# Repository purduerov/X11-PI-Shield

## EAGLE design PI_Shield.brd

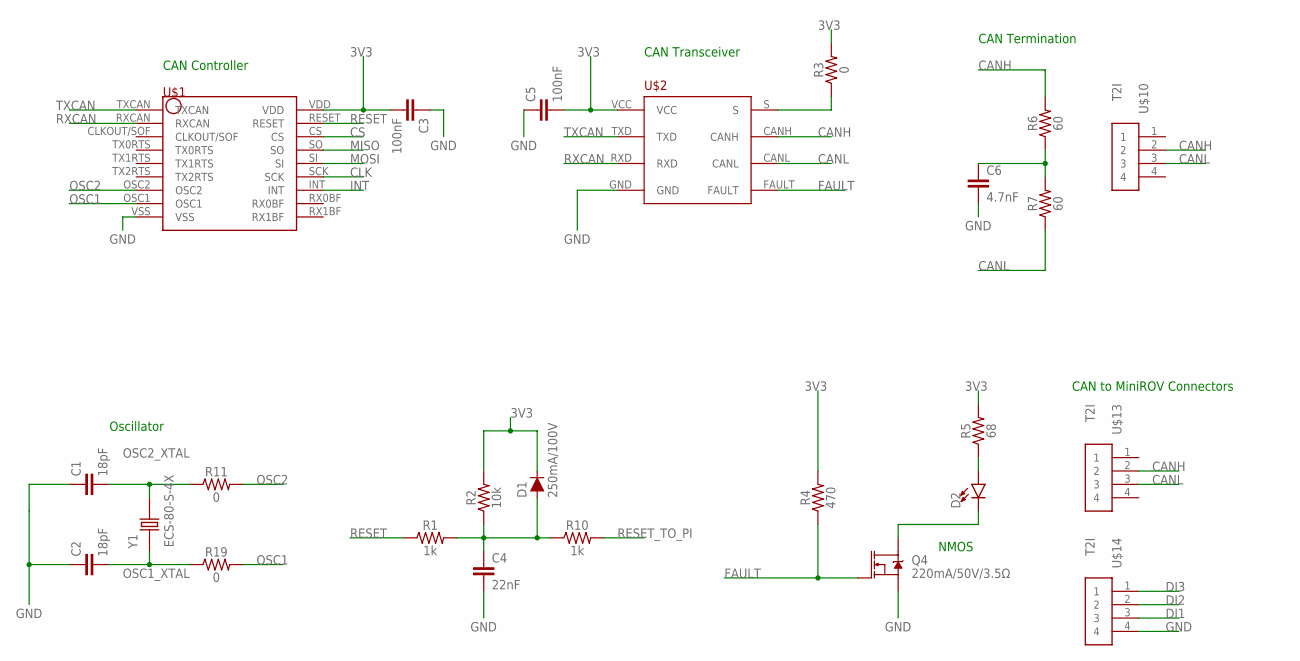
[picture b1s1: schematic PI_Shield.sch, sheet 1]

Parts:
C1, C2: 18pF; 0603
C3, C5: 100nF; 0603
C4: 22nF; 0603
C6: 4.7nF; 0603
D1: 250mA/100V; SOD-323
D2: LED0603; LED-0603
Q4: 220mA/50V/3.5Ω; SOT23-3
R1, R10: 1k; 0603
R2: 10k; 0603
R3, R11, R19: 0; 0603
R4: 470; 0603
R5: 68; 0603
R6, R7: 60; 0603
U$1: MCP2515
U$2: TCAN337D
U$10, U$13, U$14: T2I
Y1: ECS-80-S-4X; XTAL_ECS-80-S-4X

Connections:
3V3: C3.2, C5.2, D1.C, R2.2, R3.2, R4.2, R5.2, U$1.VDD, U$2.VCC; also elsewhere on the board
CANH: R6.2, U$2.CANH, U$10.2, U$13.2; also elsewhere on the board
CANL: R7.1, U$2.CANL, U$10.3, U$13.3; also elsewhere on the board
CLK: U$1.SCK; also elsewhere on the board
CS: U$1.CS; also elsewhere on the board
DI1: U$14.3; also elsewhere on the board
DI2: U$14.2; also elsewhere on the board
DI3: U$14.1; also elsewhere on the board
FAULT: Q4.1 (G), R4.1, U$2.FAULT
GND: C1.1, C2.1, C3.1, C4.2, C5.1, C6.2, Q4.2 (S), U$1.VSS, U$2.GND, U$14.4; also elsewhere on the board
INT: U$1.INT; also elsewhere on the board
MISO: U$1.SO; also elsewhere on the board
MOSI: U$1.SI; also elsewhere on the board
unnamed: R3.1, U$2.S
unnamed: C6.1, R6.1, R7.2
unnamed: C4.1, D1.A, R1.2, R2.1, R10.1
unnamed: D2.C, Q4.3 (D)
unnamed: D2.A, R5.1
OSC1: R19.2, U$1.OSC1
OSC1_XTAL: C2.2, R19.1, Y1.1
OSC2: R11.2, U$1.OSC2
OSC2_XTAL: C1.2, R11.1, Y1.2
RESET: R1.1, U$1.RESET
RESET_TO_PI: R10.2; also elsewhere on the board
RXCAN: U$1.RXCAN, U$2.RXD
TXCAN: U$1.TXCAN, U$2.TXD

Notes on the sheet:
NMOS
CAN Controller
CAN Transceiver
Oscillator
CAN Termination
CAN to MiniROV Connectors

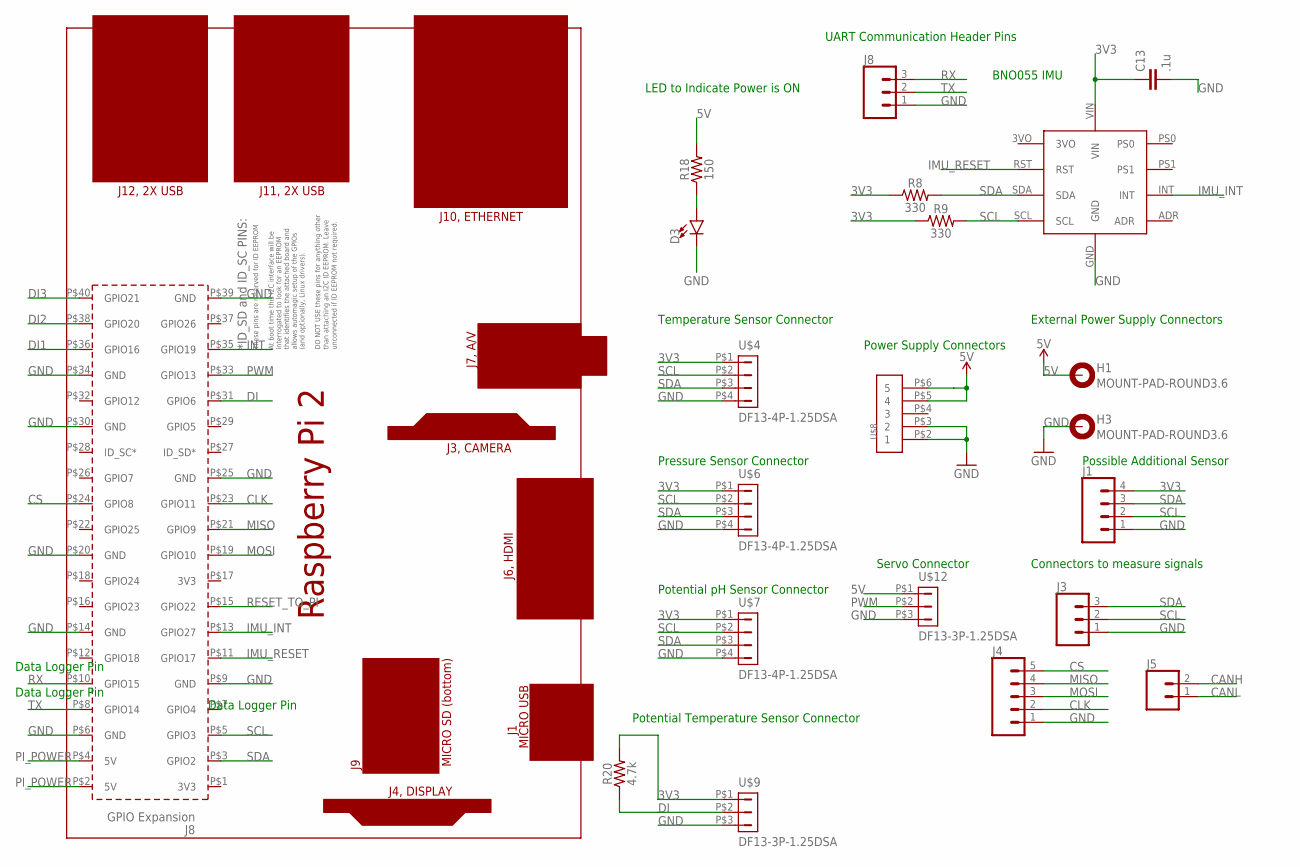
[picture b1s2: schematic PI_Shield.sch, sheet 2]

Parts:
C13: .1u; 0603
D3: LED0603; LED-0603
H1, H3: MOUNT-PAD-ROUND3.6; 3,6-PAD
J1: CONN_04; 1X04
J3, J8: CONN_03; 1X03
J4: CONN_05; 1X05
J5: CONN_02; 1X02
PCB1: RPI2
R8, R9: 330; 0603
R18: 150; 0603
R20: 4.7k; 0603
U$3: BNO055_9DOF_BREAKOUT; BNO055
U$4, U$6, U$7: DF13-4P-1.25DSA
U$8: T2I5P
U$9, U$12: DF13-3P-1.25DSA

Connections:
3V3: C13.1, J1.4, R8.1, R9.1, R20.2, U$3.VIN, U$4.P$1 (1), U$6.P$1 (1), U$7.P$1 (1), U$9.P$1 (1); also elsewhere on the board
5V: H1.B3,6, R18.2, U$8.P$5 (4), U$8.P$6 (5), U$12.P$1 (1); also elsewhere on the board
CANH: J5.2; also elsewhere on the board
CANL: J5.1; also elsewhere on the board
CLK: J4.2, PCB1.P$23 (GPIO11); also elsewhere on the board
CS: J4.5, PCB1.P$24 (GPIO8); also elsewhere on the board
DI: PCB1.P$31 (GPIO6), R20.1, U$9.P$2 (2)
DI1: PCB1.P$36 (GPIO16); also elsewhere on the board
DI2: PCB1.P$38 (GPIO20); also elsewhere on the board
DI3: PCB1.P$40 (GPIO21); also elsewhere on the board
GND: C13.2, D3.C, H3.B3,6, J1.1, J3.1, J4.1, J8.1, PCB1.P$6 (GND), PCB1.P$9 (GND), PCB1.P$14 (GND), PCB1.P$20 (GND), PCB1.P$25 (GND), PCB1.P$30 (GND), PCB1.P$34 (GND), PCB1.P$39 (GND), U$3.GND, U$4.P$4 (4), U$6.P$4 (4), U$7.P$4 (4), U$8.P$2 (1), U$8.P$3 (2), U$9.P$3 (3), U$12.P$3 (3); also elsewhere on the board
IMU_INT: PCB1.P$13 (GPIO27), U$3.INT
IMU_RESET: PCB1.P$11 (GPIO17), U$3.RST
INT: PCB1.P$35 (GPIO19); also elsewhere on the board
MISO: J4.4, PCB1.P$21 (GPIO9); also elsewhere on the board
MOSI: J4.3, PCB1.P$19 (GPIO10); also elsewhere on the board
unnamed: D3.A, R18.1
PI_POWER: PCB1.P$2 (5V), PCB1.P$4 (5V); also elsewhere on the board
PWM: PCB1.P$33 (GPIO13), U$12.P$2 (2)
RESET_TO_PI: PCB1.P$15 (GPIO22); also elsewhere on the board
RX: J8.3, PCB1.P$10 (GPIO15)
SCL: J1.2, J3.2, PCB1.P$5 (GPIO3), R9.2, U$3.SCL, U$4.P$2 (2), U$6.P$2 (2), U$7.P$2 (2); also elsewhere on the board
SDA: J1.3, J3.3, PCB1.P$3 (GPIO2), R8.2, U$3.SDA, U$4.P$3 (3), U$6.P$3 (3), U$7.P$3 (3); also elsewhere on the board
TX: J8.2, PCB1.P$8 (GPIO14)

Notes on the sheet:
Connectors to measure signals
Temperature Sensor Connector
Pressure Sensor Connector
Potential pH Sensor Connector
BNO055 IMU
External Power Supply Connectors
LED to Indicate Power is ON
Potential Temperature Sensor Connector
Power Supply Connectors
Data Logger Pin
Possible Additional Sensor
UART Communication Header Pins
Servo Connector

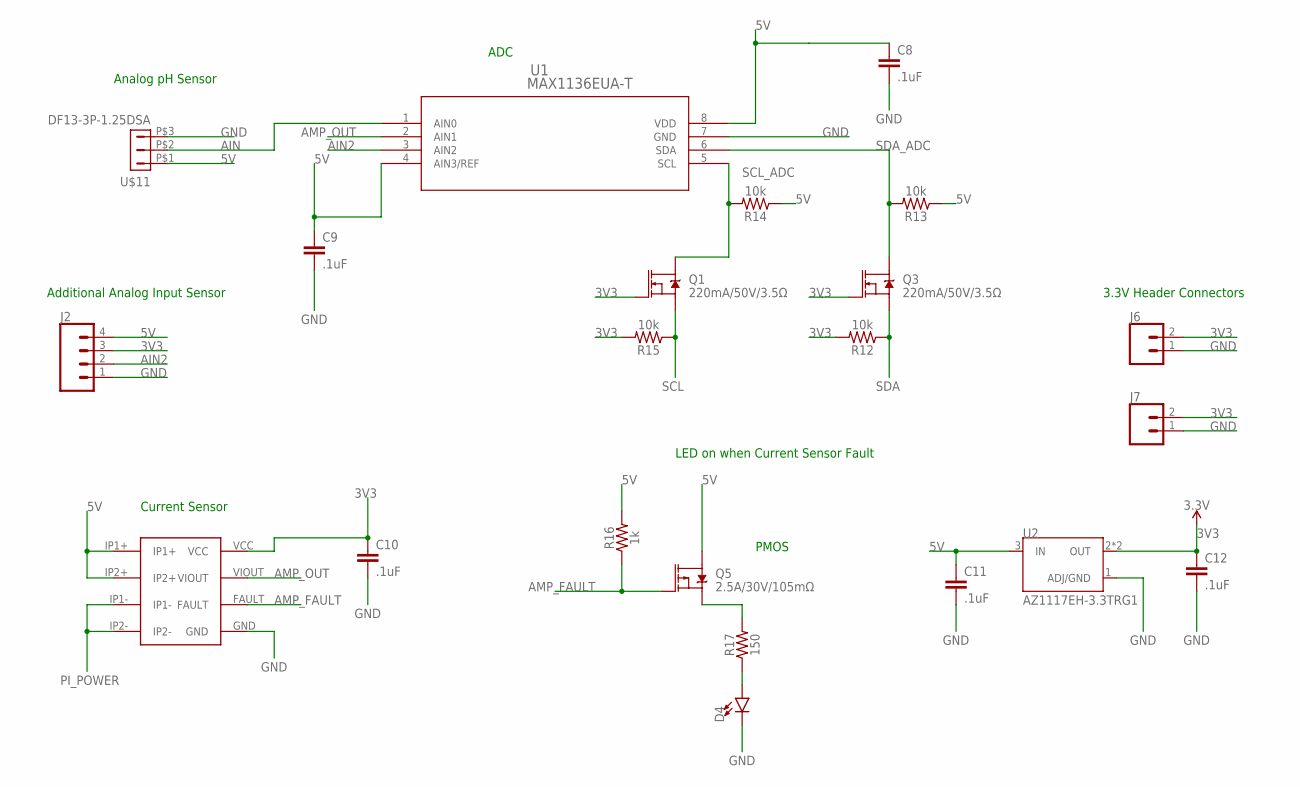
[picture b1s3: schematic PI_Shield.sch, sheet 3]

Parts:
C8, C9, C10, C11, C12: .1uF; 0603
D4: LED0603; LED-0603
J2: CONN_04; 1X04
J6, J7: CONN_02; 1X02
Q1, Q3: 220mA/50V/3.5Ω; SOT23-3
Q5: 2.5A/30V/105mΩ; SOT23-3
R12, R13, R14, R15: 10k; 0603
R16: 1k; 0603
R17: 150; 0603
U1: MAX1136EUA-T; 21-0036K
U2: AZ1117EH-3.3TRG1; SOT230P700X180-4N
U$5: ACS711
U$11: DF13-3P-1.25DSA

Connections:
3V3: C10.1, C12.1, J2.3, J6.2, J7.2, Q1.1 (G), Q3.1 (G), R12.2, R15.2, U2.2 (OUT), U2.4 (OUT), U$5.VCC; also elsewhere on the board
5V: C8.1, C9.1, C11.1, J2.4, Q5.3 (D), R13.1, R14.1, R16.2, U1.4 (AIN3/REF), U1.8 (VDD), U2.3 (IN), U$5.IP1+, U$5.IP2+, U$11.P$1 (1); also elsewhere on the board
AIN: U1.1 (AIN0), U$11.P$2 (2)
AIN2: J2.2, U1.3 (AIN2)
AMP_FAULT: Q5.1 (G), R16.1, U$5.FAULT
AMP_OUT: U1.2 (AIN1), U$5.VIOUT
GND: C8.2, C9.2, C10.2, C11.2, C12.2, D4.C, J2.1, J6.1, J7.1, U1.7 (GND), U2.1 (ADJ/GND), U$5.GND, U$11.P$3 (3); also elsewhere on the board
unnamed: Q5.2 (S), R17.2
unnamed: D4.A, R17.1
PI_POWER: U$5.IP1-, U$5.IP2-; also elsewhere on the board
SCL: Q1.2 (S), R15.1; also elsewhere on the board
SCL_ADC: Q1.3 (D), R14.2, U1.5 (SCL)
SDA: Q3.2 (S), R12.1; also elsewhere on the board
SDA_ADC: Q3.3 (D), R13.2, U1.6 (SDA)

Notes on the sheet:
Analog pH Sensor
PMOS
ADC
Current Sensor
LED on when Current Sensor Fault
Additional Analog Input Sensor
3.3V Header Connectors

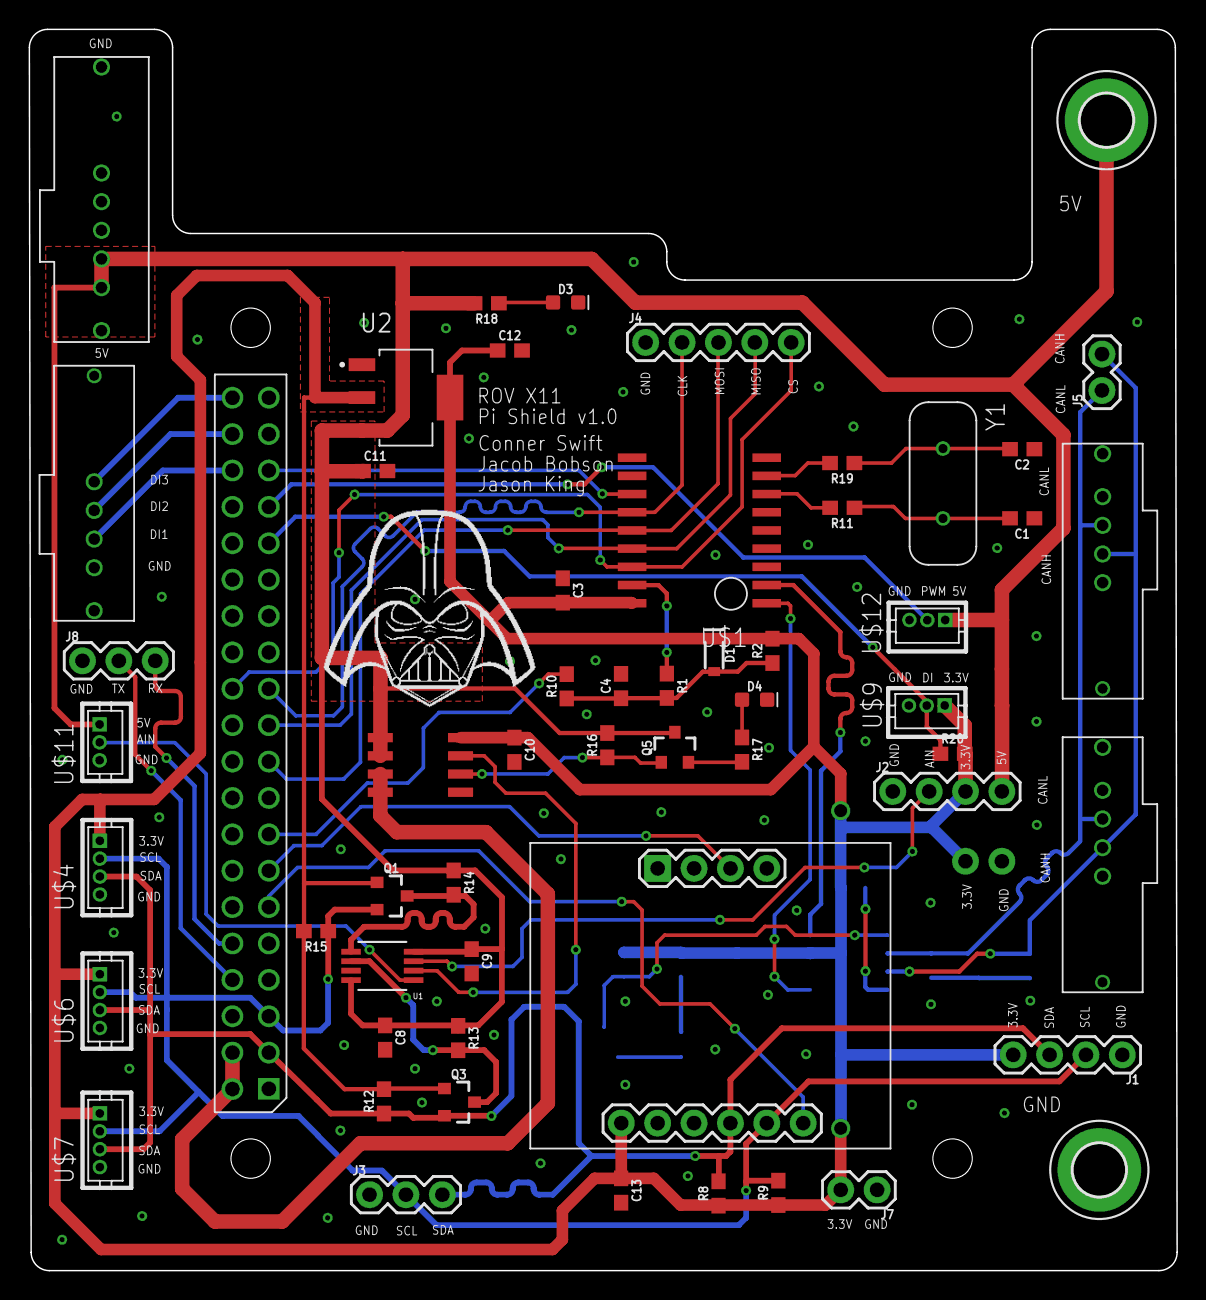
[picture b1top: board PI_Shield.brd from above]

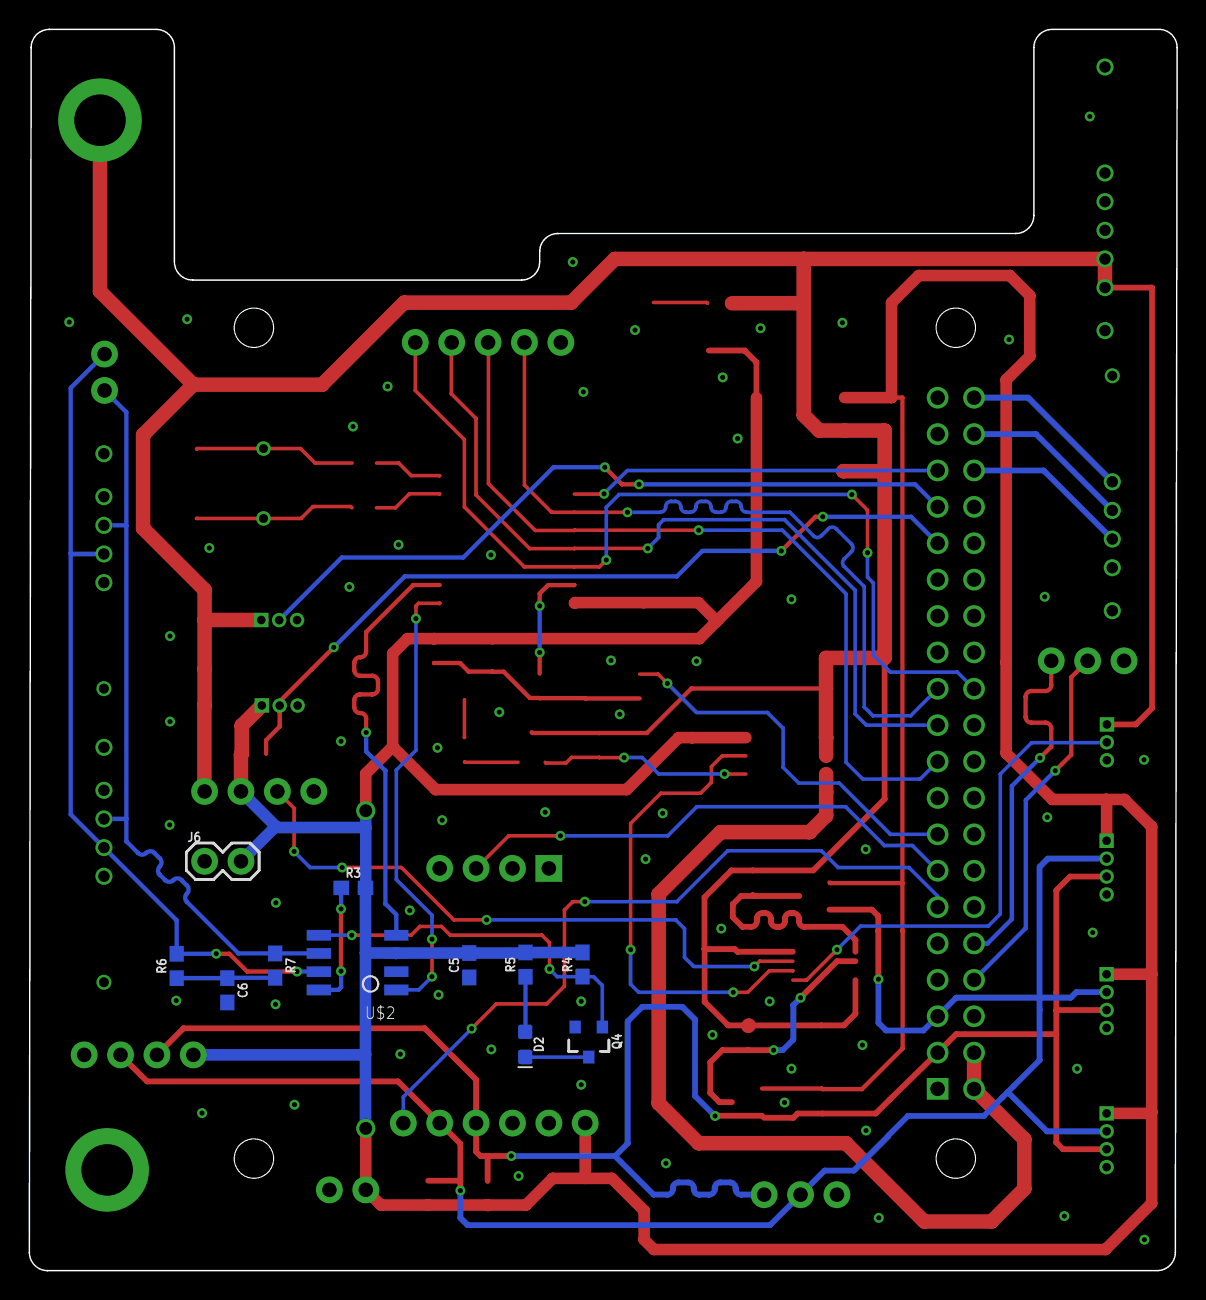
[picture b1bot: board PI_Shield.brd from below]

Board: 2 copper layers, 80.1 x 86.7 mm, 68 parts (11 on the bottom side), 45 nets.

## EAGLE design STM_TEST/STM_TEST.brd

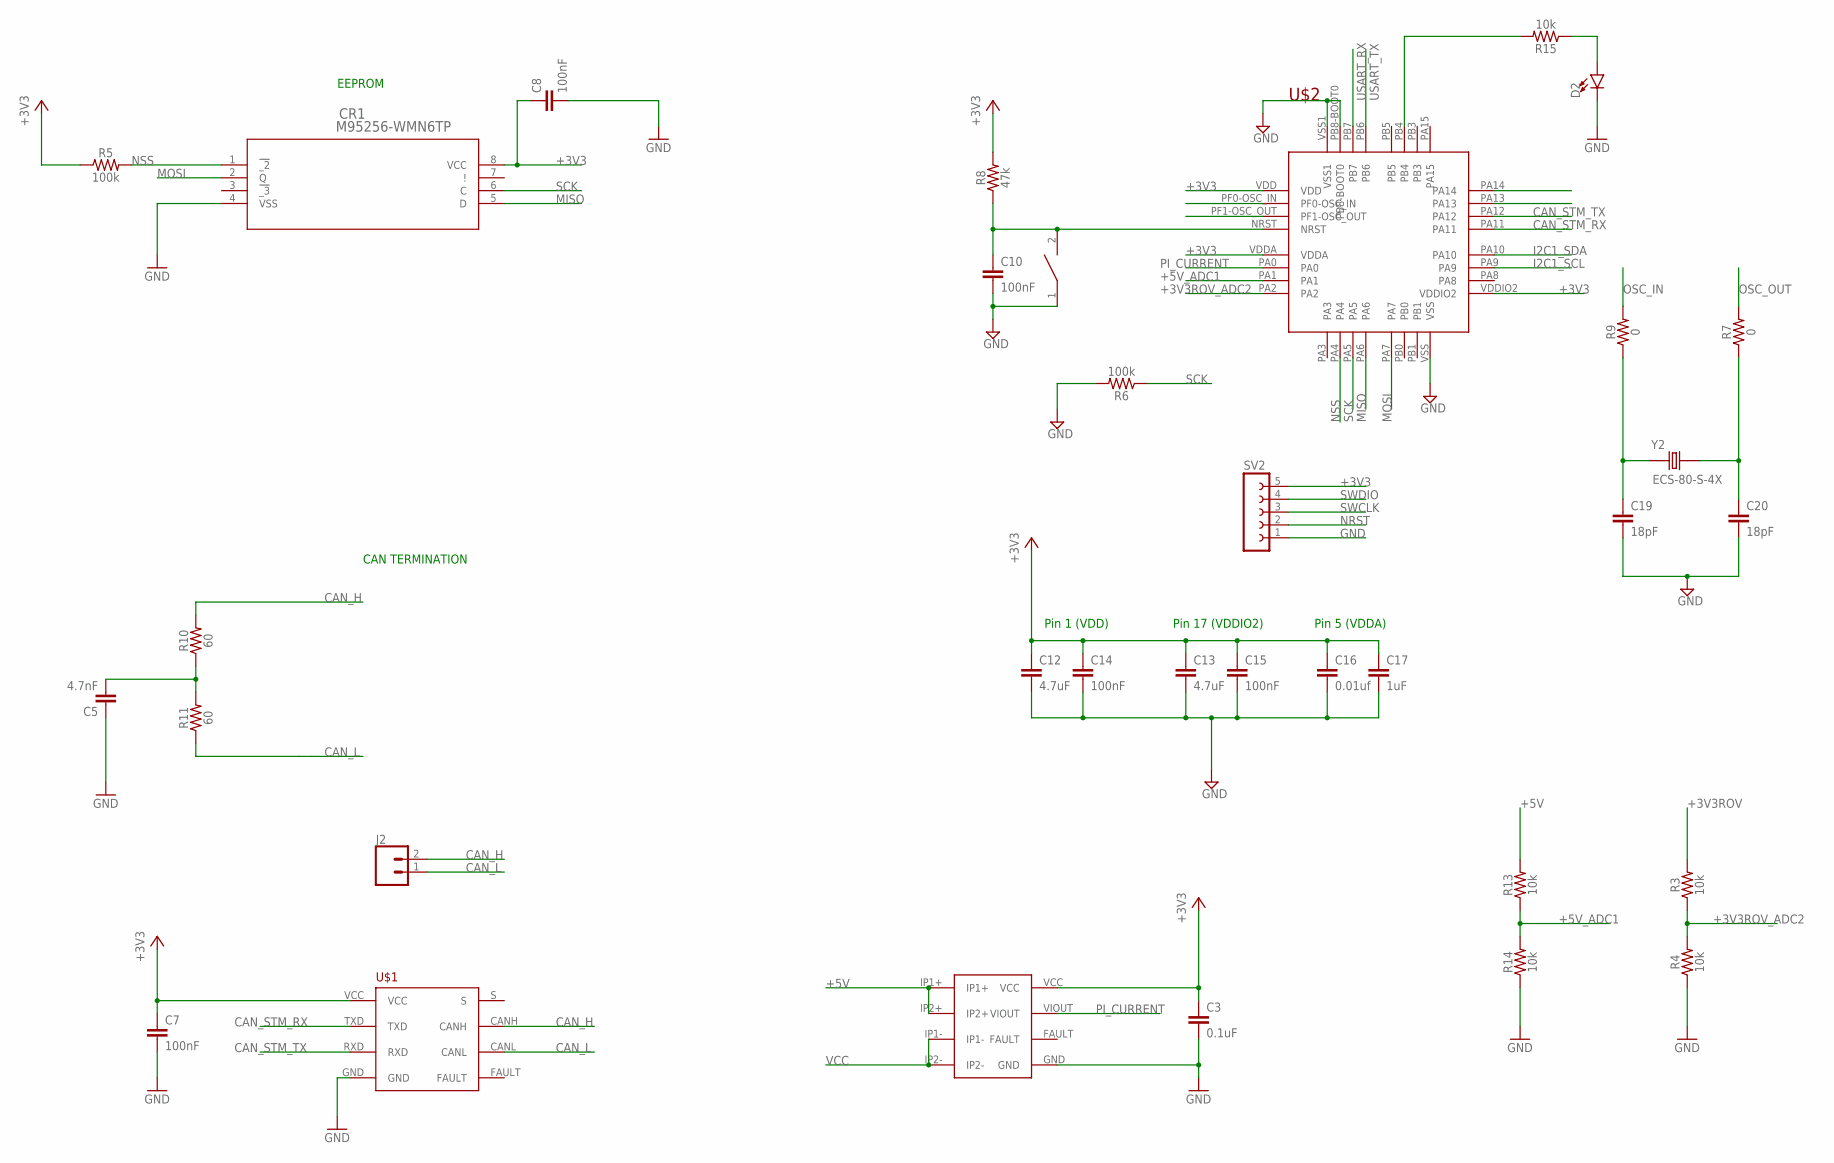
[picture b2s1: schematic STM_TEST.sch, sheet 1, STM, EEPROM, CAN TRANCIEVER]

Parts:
C3: 0.1uF; 0603
C5: 4.7nF; 0603
C7, C8, C10, C14, C15: 100nF; 0603
C12, C13: 4.7uF; 0603
C16: 0.01uf; 0603
C17: 1uF; 0603
C19, C20: 18pF; 0603
CR1: M95256-WMN6TP; SO-8
D2: LED0603; LED-0603
J2: CONN_02; 1X02
R3, R4, R13, R14, R15: 10k; 0603
R5, R6: 100k; 0603
R7, R9: 0; 0603
R8: 47k; 0603
R10, R11: 60; 0603
RESET1: SWITCH; SW_2512
SV2: FE05-1
U$1: TCAN337D
U$2: STM32F042K6T6
U$4: ACS711
Y2: ECS-80-S-4X; XTAL_ECS-80-S-4X

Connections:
+3V3: C3.1, C7.1, C8.1, C12.1, C13.1, C14.1, C15.1, C16.1, C17.1, CR1.8 (VCC), R5.1, R8.2, SV2.5, U$1.VCC, U$2.VDD, U$2.VDDA, U$2.VDDIO2, U$4.VCC; also elsewhere on the board
+3V3ROV: R3.2; also elsewhere on the board
+3V3ROV_ADC2: R3.1, R4.2, U$2.PA2
+5V: R13.2, U$4.IP1+, U$4.IP2+; also elsewhere on the board
+5V_ADC1: R13.1, R14.2, U$2.PA1
CAN_H: J2.2, R10.2, U$1.CANH; also elsewhere on the board
CAN_L: J2.1, R11.1, U$1.CANL; also elsewhere on the board
CAN_STM_RX: U$1.TXD, U$2.PA11
CAN_STM_TX: U$1.RXD, U$2.PA12
GND: C3.2, C5.1, C7.2, C8.2, C10.2, C12.2, C13.2, C14.2, C15.2, C16.2, C17.2, C19.2, C20.2, CR1.4 (VSS), D2.C, R4.1, R6.2, R14.1, RESET1.1, SV2.1, U$1.GND, U$2.PB8-BOOT0, U$2.VSS, U$2.VSS1, U$4.GND; also elsewhere on the board
I2C1_SCL: U$2.PA9; also elsewhere on the board
I2C1_SDA: U$2.PA10; also elsewhere on the board
MISO: CR1.5 (D), U$2.PA6
MOSI: CR1.2 (Q), U$2.PA7
unnamed: C5.2, R10.1, R11.2
unnamed: D2.A, R15.1
unnamed: R15.2, U$2.PB4
unnamed: C20.1, R7.1, Y2.2
unnamed: C19.1, R9.1, Y2.1
NRST: C10.1, R8.1, RESET1.2, SV2.2, U$2.NRST
NSS: CR1.1 (!_2), R5.2, U$2.PA4
OSC_IN: R9.2, U$2.PF0-OSC_IN
OSC_OUT: R7.2, U$2.PF1-OSC_OUT
PI_CURRENT: U$2.PA0, U$4.VIOUT
SCK: CR1.6 (C), R6.1, U$2.PA5
SWCLK: SV2.3, U$2.PA14
SWDIO: SV2.4, U$2.PA13
USART_RX: U$2.PB7; also elsewhere on the board
USART_TX: U$2.PB6; also elsewhere on the board
VCC: U$4.IP1-, U$4.IP2-; also elsewhere on the board

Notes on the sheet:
Pin 1 (VDD)
Pin 17 (VDDIO2)
Pin 5 (VDDA)
CAN TERMINATION
EEPROM

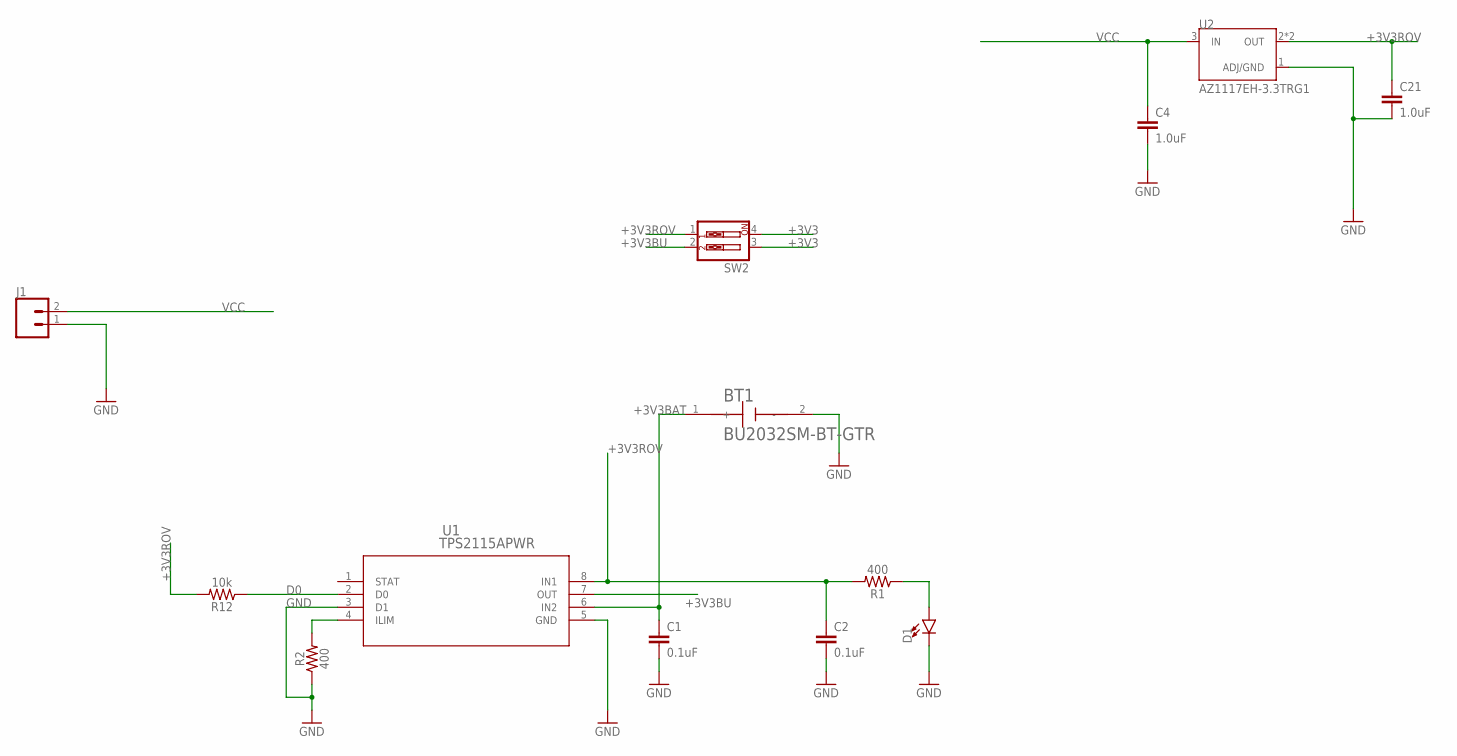
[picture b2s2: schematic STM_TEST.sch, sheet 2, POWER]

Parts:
BT1: BU2032SM-BT-GTR; BAT_BU2032SM-BT-GTR
C1, C2: 0.1uF; 0603
C4, C21: 1.0uF; 0603
D1: LED0603; LED-0603
J1: CONN_02; 1X02
R1, R2: 400; 0603
R12: 10k; 0603
SW2: SW_DIP-2; EDG-02
U1: TPS2115APWR; PW8
U2: AZ1117EH-3.3TRG1; SOT230P700X180-4N

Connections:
+3V3: SW2.3, SW2.4; also elsewhere on the board
+3V3BAT: BT1.1 (+), C1.1, U1.6 (IN2)
+3V3BU: SW2.2, U1.7 (OUT)
+3V3ROV: C2.1, C21.1, R1.2, R12.2, SW2.1, U1.8 (IN1), U2.2 (OUT), U2.4 (OUT); also elsewhere on the board
D0: R12.1, U1.2 (D0)
GND: BT1.2 (-), C1.2, C2.2, C4.2, C21.2, D1.C, J1.1, R2.1, U1.3 (D1), U1.5 (GND), U2.1 (ADJ/GND); also elsewhere on the board
unnamed: R2.2, U1.4 (ILIM)
unnamed: D1.A, R1.1
VCC: C4.1, J1.2, U2.3 (IN); also elsewhere on the board

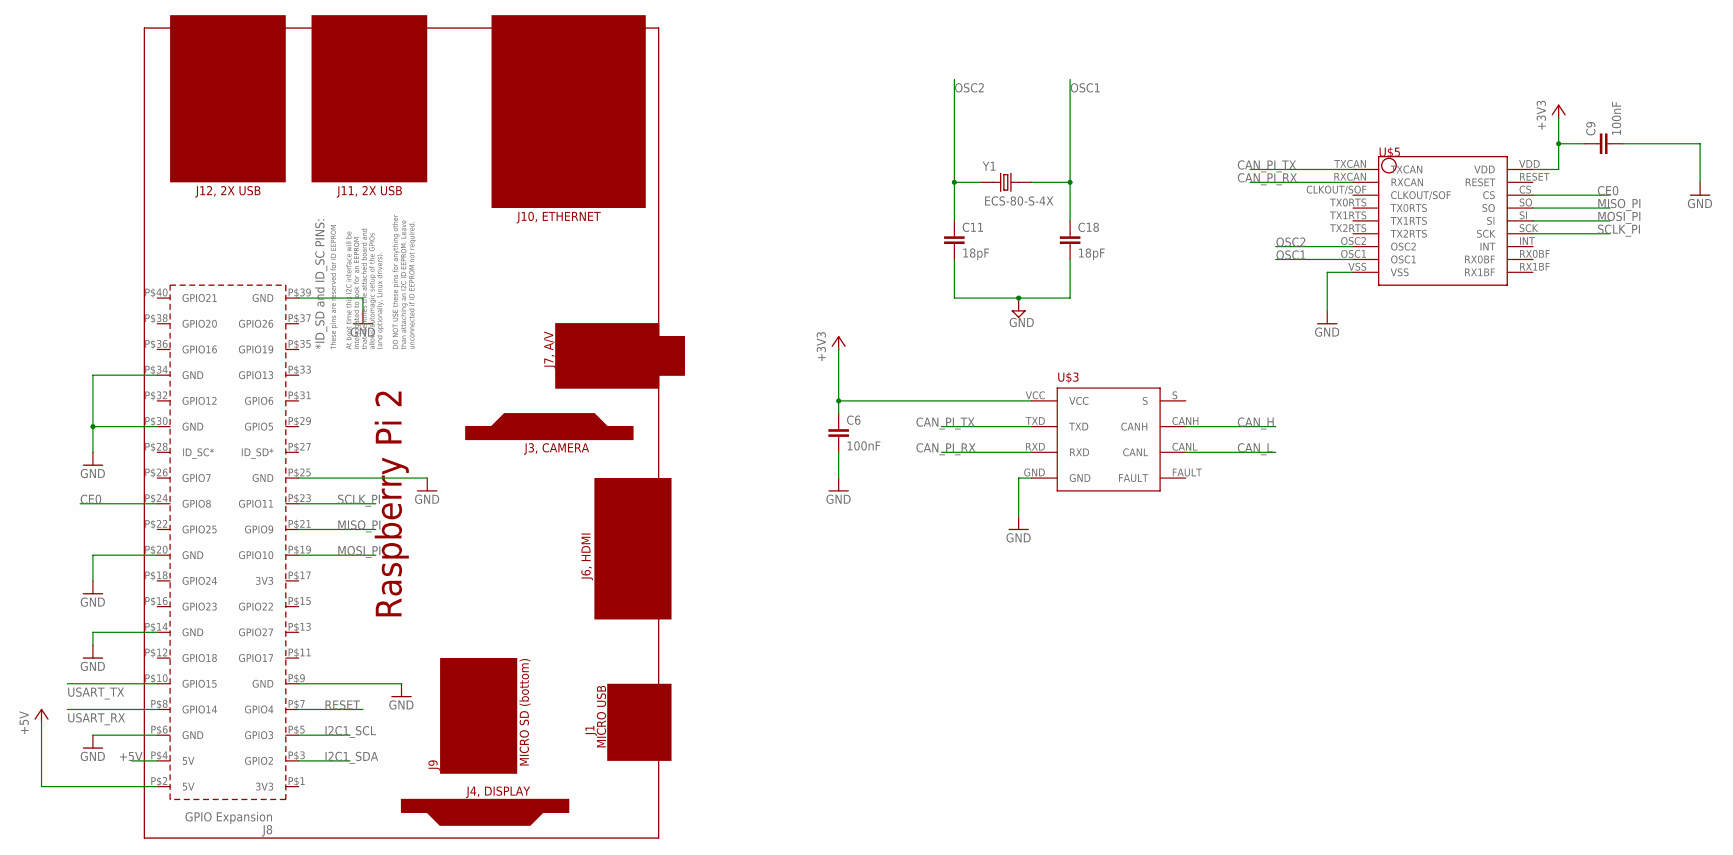
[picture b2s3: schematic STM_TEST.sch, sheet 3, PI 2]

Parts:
C6, C9: 100nF; 0603
C11, C18: 18pF; 0603
PCB1: RPI2
U$3: TCAN337D
U$5: MCP2515
Y1: ECS-80-S-4X; XTAL_ECS-80-S-4X

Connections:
+3V3: C6.1, C9.1, U$3.VCC, U$5.VDD; also elsewhere on the board
+5V: PCB1.P$2 (5V), PCB1.P$4 (5V); also elsewhere on the board
CAN_H: U$3.CANH; also elsewhere on the board
CAN_L: U$3.CANL; also elsewhere on the board
CAN_PI_RX: U$3.RXD, U$5.RXCAN
CAN_PI_TX: U$3.TXD, U$5.TXCAN
CE0: PCB1.P$24 (GPIO8), U$5.CS
GND: C6.2, C9.2, C11.2, C18.2, PCB1.P$6 (GND), PCB1.P$9 (GND), PCB1.P$14 (GND), PCB1.P$20 (GND), PCB1.P$25 (GND), PCB1.P$30 (GND), PCB1.P$34 (GND), PCB1.P$39 (GND), U$3.GND, U$5.VSS; also elsewhere on the board
I2C1_SCL: PCB1.P$5 (GPIO3); also elsewhere on the board
I2C1_SDA: PCB1.P$3 (GPIO2); also elsewhere on the board
MISO_PI: PCB1.P$21 (GPIO9), U$5.SO
MOSI_PI: PCB1.P$19 (GPIO10), U$5.SI
OSC1: C18.1, U$5.OSC1, Y1.2
OSC2: C11.1, U$5.OSC2, Y1.1
RESET: PCB1.P$7 (GPIO4)
SCLK_PI: PCB1.P$23 (GPIO11), U$5.SCK
USART_RX: PCB1.P$8 (GPIO14); also elsewhere on the board
USART_TX: PCB1.P$10 (GPIO15); also elsewhere on the board

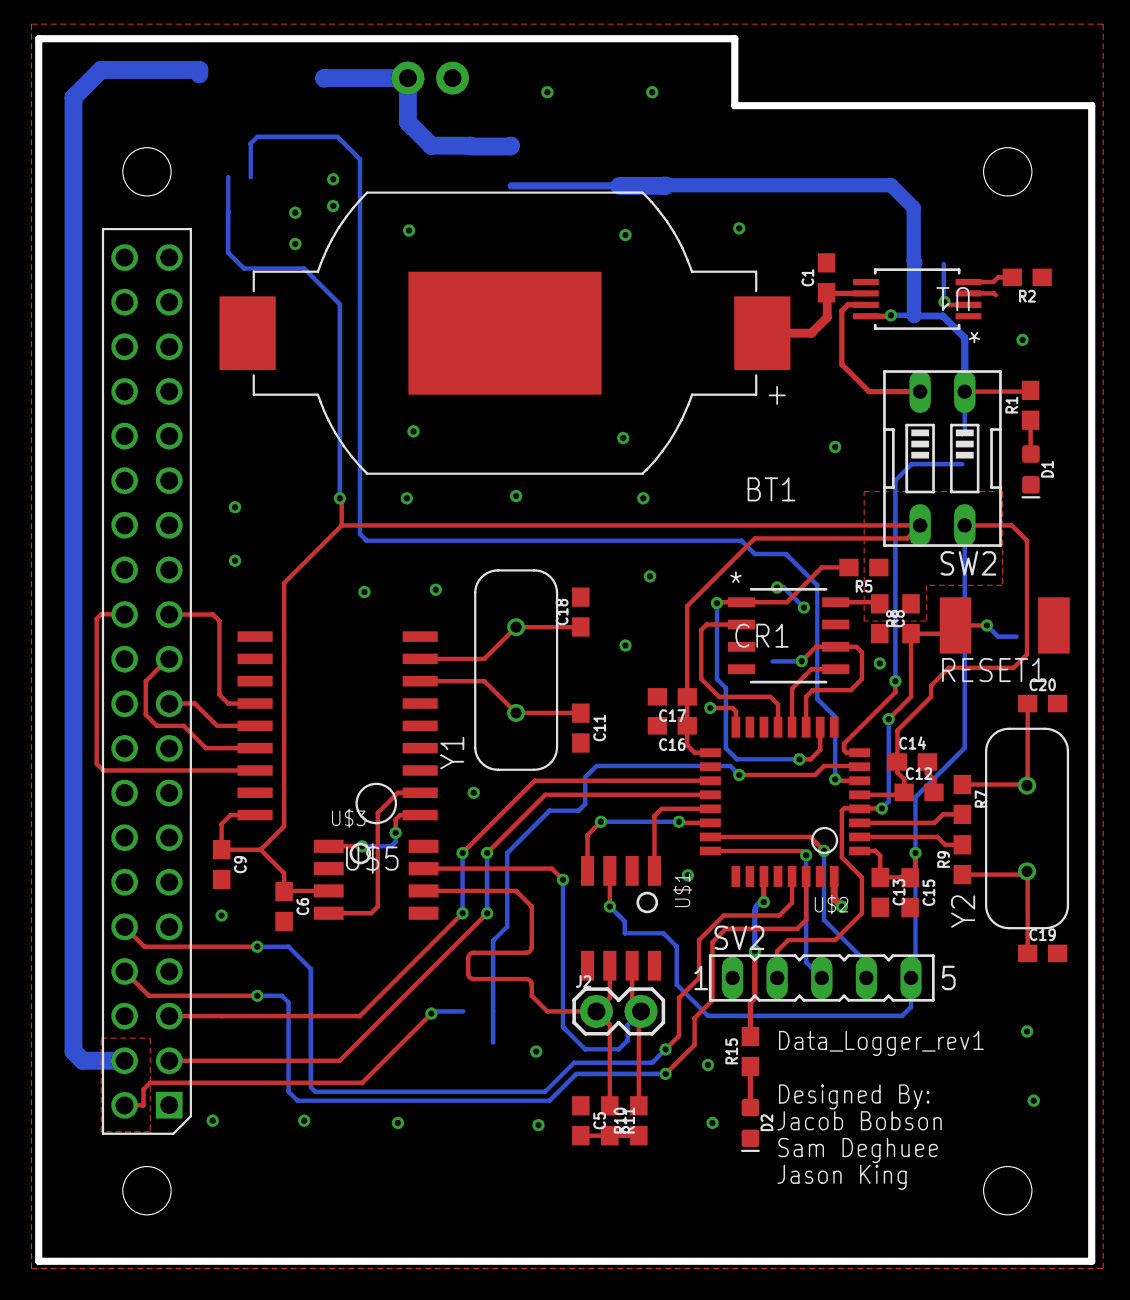
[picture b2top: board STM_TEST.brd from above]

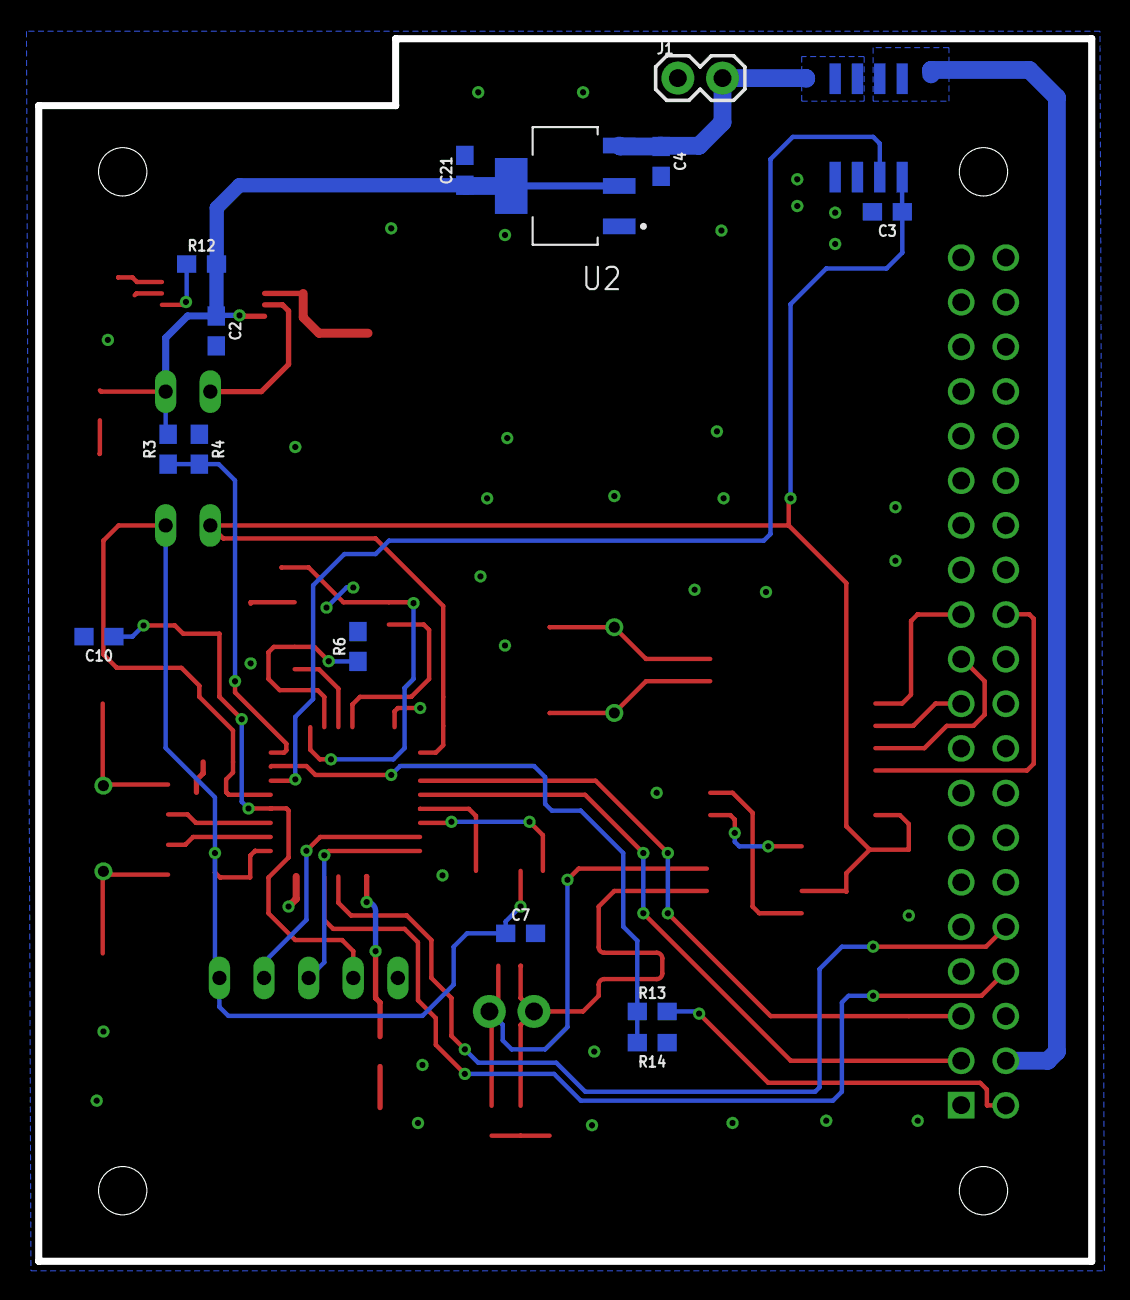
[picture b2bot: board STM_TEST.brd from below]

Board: 2 copper layers, 59.9 x 69.6 mm, 55 parts (15 on the bottom side), 43 nets.

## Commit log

2018-09-19 added gitignore
2018-10-16 Test Board for STM and Data Logger
2018-10-16 Routing and Stuff
2018-10-16 More Stuff
2018-10-16 Board Dimensions and Connector Layout
2018-10-16 Y'all Like Samtech?
2018-10-17 Yay CAN
2018-10-17 Board Layout
2018-10-17 things
2018-10-19 reroute
2018-10-23 Rerouting
2018-10-23 routing
2018-10-24 uhhh, yeah boards looking good
2018-10-25 Routing Complete
2018-10-25 Added some gnd vias
2018-10-25 Fixed Silk Screen
2018-10-25 Routed USART
2018-10-27 Added Pi Shield Schematic
2018-10-27 Made Changes to Schematic
2018-10-31 Minor Changes with Schematic
2018-11-10 Starting to Route Board
2018-11-27 Added Current Sensor
2018-11-27 finished
2018-12-01 Almost Done with Board
2018-12-01 Almost Done
2018-12-01 Minor Changes to Board
2018-12-15 Minor Changes to Pi Shield
2018-12-27 Added Connectors, need to route
2018-12-27 Most of Changes done, need to impedance match
2018-12-28 Changes done
2018-12-28 More Changes
2018-12-28 Even more changes
2019-01-03 Added Silkscreen Text
2019-01-04 Fixed connector inputs for sensors to match blue robotics website
2019-01-11 switched power from 5v to 3.3v on dallas temperature sensor
2019-02-04 Hopefully this works or Cynthia

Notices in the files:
parts and their libraries:
SparkFun-Capacitors: Licensing: Creative Commons ShareAlike 4.0 International - https://creativecommons.org/licenses/by-sa/4.0
